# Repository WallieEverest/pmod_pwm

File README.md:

# Overview

This circuit is a PWM audio filter for the TT04 ChipTune project.
ChipTune replicates the Audio Processing Unit (APU) of vintage video games.
Separate PWM outputs are provided for each sound engine, allowing NES game music to be externally mixed into stereo or surround sound.
Resistor values will be tailored for balancing channel volume.

The primary interface is PMOD connectors to the TT04 Breakout Board. Final layout is pending assignment of all three PMOD connectors.

Based on data from:
- https://github.com/WallieEverest/tt04

## Interface

- UI_IN PMOD
- UO_OUT PMOD
- UIO PMOD (unused)
- USB-B for serial UART control of the Tiny Tapeout project
- JST 3-pin connector for low-level stereo preamp
- Onboard speaker for demonstrations

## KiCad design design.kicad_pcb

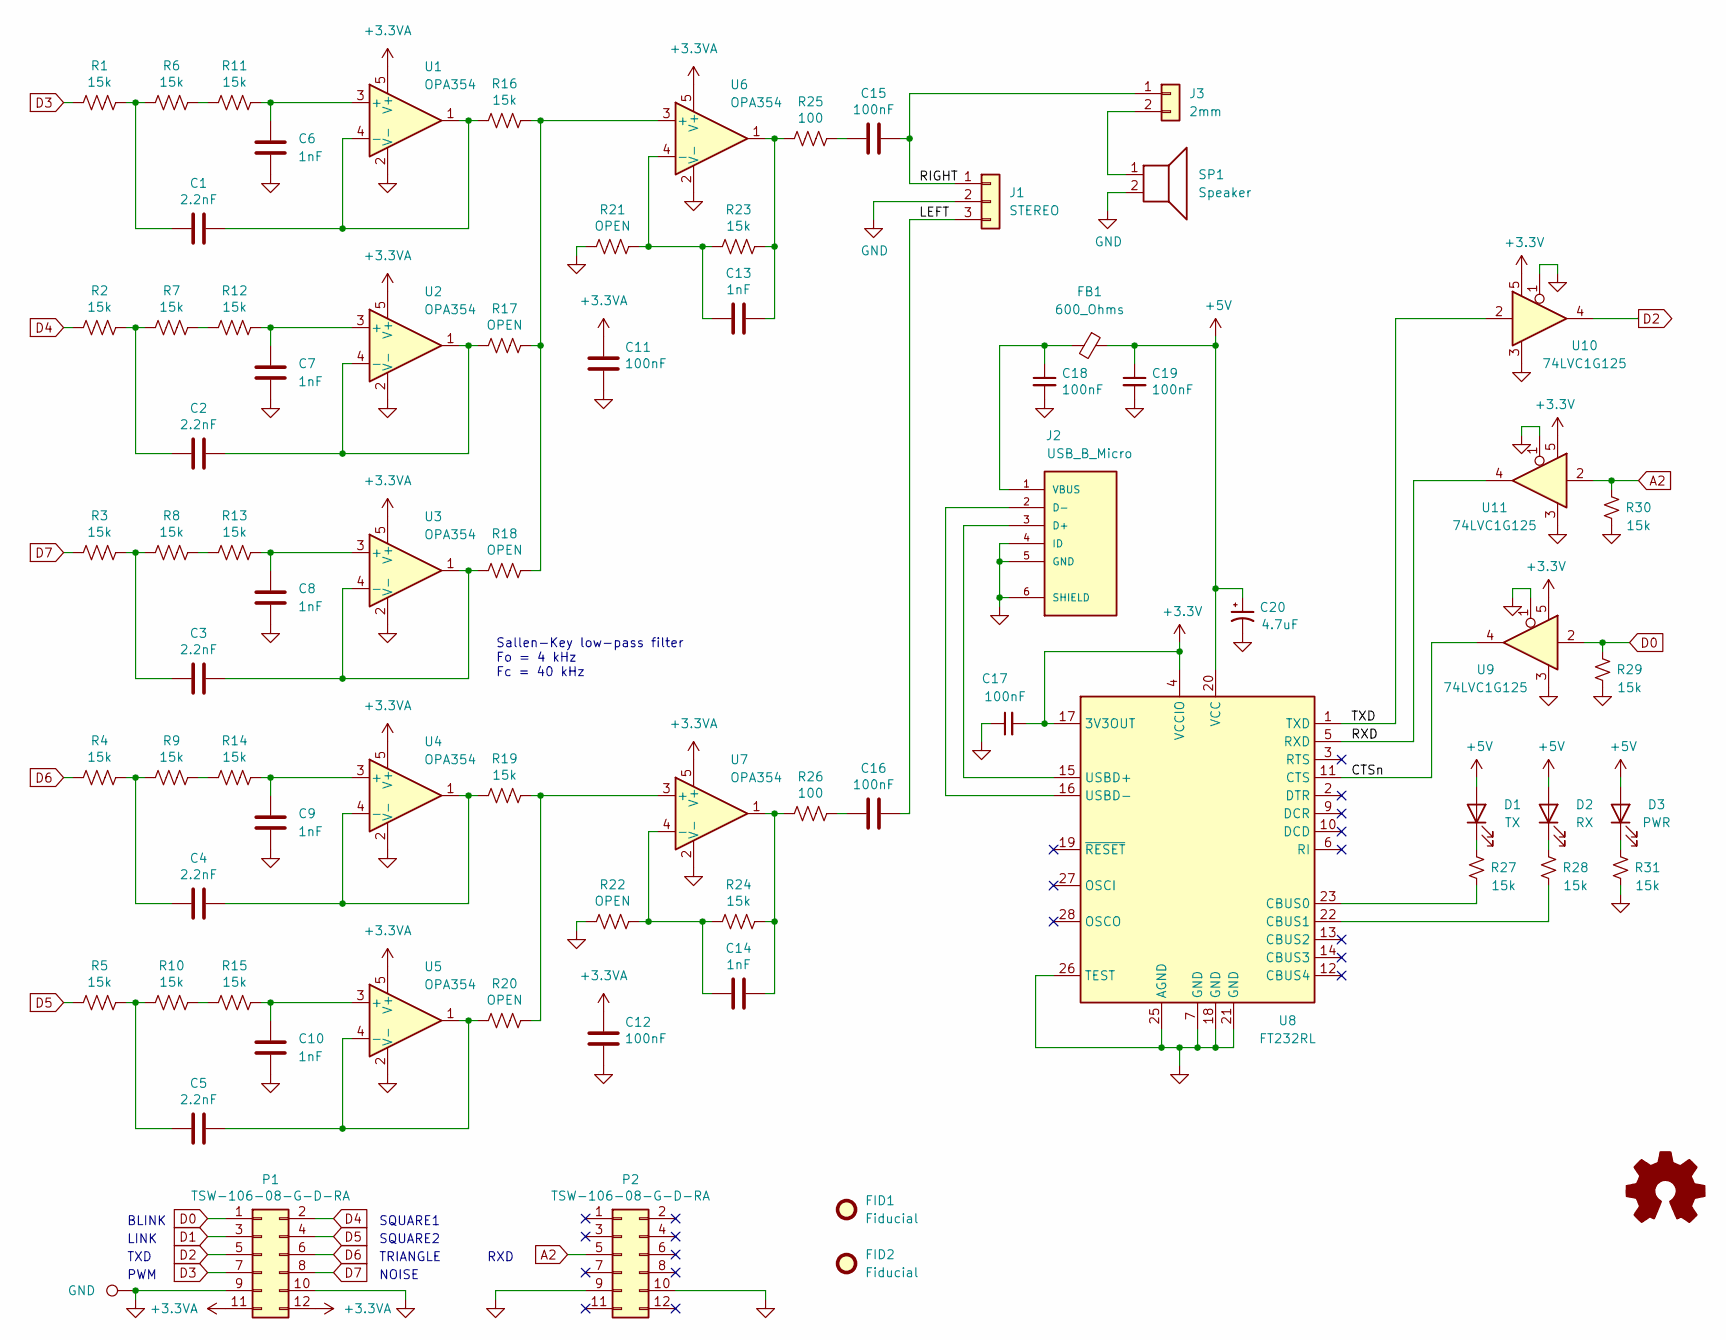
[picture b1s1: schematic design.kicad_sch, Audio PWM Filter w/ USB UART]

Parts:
C1, C2, C3, C4, C5: 2.2nF; C_0402_1005Metric; LCSC C913886
C6, C7, C8, C9, C10, C13, C14: 1nF; C_0402_1005Metric; LCSC C1523
C11, C12, C15, C16, C17, C18, C19: 100nF; C_0402_1005Metric; LCSC C1525
C20: 4.7uF; C_0603_1608Metric; LCSC C19666
D1: TX; LED_0805_2012Metric_Castellated; LCSC C2297
D2: RX; LED_0805_2012Metric_Castellated; LCSC C2297
D3: PWR; LED_0805_2012Metric_Castellated; LCSC C2297
FB1: 600_Ohms; L_0805_2012Metric; LCSC C1017
FID1, FID2: Fiducial; Fiducial_0.75mm_Mask1.5mm; LCSC None
J1: STEREO; JST_SH_BM03B-SRSS-TB_1x03-1MP_P1.00mm_Vertical; LCSC C160389
J2: USB_B_Micro; SHOUHAN_MICROXNJ; LCSC C404969
J3: 2mm; PinHeader_1x02_P2.00mm_Vertical_SMD_Pin1Left; LCSC C917549
P1, P2: TSW-106-08-G-D-RA; PinHeader_2x06_PMOD; LCSC C706887
R1, R2, R3, R4, R5, R6, R7, R8, R9, R10, R11, R12, R13, R14, R15, R16, R19, R23, R24, R27, R28, R29, R30, R31: 15k; R_0402_1005Metric; LCSC C25756
R17, R18, R20, R21, R22: OPEN; R_0402_1005Metric; LCSC C26083
R25, R26: 100; R_0402_1005Metric; LCSC C25076
SP1: Speaker; speaker_fs_1340; LCSC C482342
TP1: GND; TestPoint_Keystone_5019_Minature; LCSC C5199800
U1, U2, U3, U4, U5, U6, U7: OPA354; SOT-23-5_OPA; LCSC C36384
U8: FT232RL; SSOP-28_5.3x10.2mm_P0.65mm; LCSC C8690
U9, U10, U11: 74LVC1G125; SOT-23-5; LCSC C23654

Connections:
+3.3VA: C11.1, C12.1, P1.11, P1.12, U1.5 (V+), U2.5 (V+), U3.5 (V+), U4.5 (V+), U5.5 (V+), U6.5 (V+), U7.5 (V+)
+3V3: C17.2, U8.4 (VCCIO), U8.17 (3V3OUT), U9.5 (VCC), U10.5 (VCC), U11.5 (VCC)
+5V: C19.1, C20.1, D1.2 (A), D2.2 (A), D3.2 (A), FB1.1, U8.20 (VCC)
/CTSn: U8.11 (CTS), U9.4
/LEFT: C16.1, J1.3
/RIGHT: C15.1, J1.1, J3.1
/RXD: U8.5 (RXD), U11.4
/TXD: U8.1 (TXD), U10.2
A2: P2.5, R30.2, U11.2
D0: P1.1, R29.2, U9.2
D1: P1.3
D2: P1.5, U10.4
D3: P1.7, R1.2
D4: P1.2, R2.2
D5: P1.4, R5.2
D6: P1.6, R4.2
D7: P1.8, R3.2
GND: C6.2, C7.2, C8.2, C9.2, C10.2, C11.2, C12.2, C17.1, C18.2, C19.2, C20.2, J1.2, J2.4 (ID), J2.5 (GND), J2.6 (SHIELD), P1.9, P1.10, P2.9, P2.10, R21.2, R22.2, R29.1, R30.1, R31.1, SP1.2, TP1.1, U1.2 (V-), U2.2 (V-), U3.2 (V-), U4.2 (V-), U5.2 (V-), U6.2 (V-), U7.2 (V-), U8.7 (GND), U8.18 (GND), U8.21 (GND), U8.25 (AGND), U8.26 (TEST), U9.1, U9.3 (GND), U10.1, U10.3 (GND), U11.1, U11.3 (GND)
unnamed: C1.2, R1.1, R6.2
unnamed: C2.2, R2.1, R7.2
unnamed: C3.2, R3.1, R8.2
unnamed: C4.2, R4.1, R9.2
unnamed: C5.2, R5.1, R10.2
unnamed: C13.1, R23.1, R25.2, U6.1
unnamed: C14.1, R24.1, R26.2, U7.1
unnamed: C15.2, R25.1
unnamed: C16.2, R26.1
unnamed: D1.1 (K), R27.2
unnamed: D2.1 (K), R28.2
unnamed: D3.1 (K), R31.2
unnamed: J2.3 (D+), U8.15 (USBD+)
unnamed: J2.2 (D-), U8.16 (USBD-)
unnamed: C18.1, FB1.2, J2.1 (VBUS)
unnamed: J3.2, SP1.1
unnamed: R10.1, R15.2
unnamed: R6.1, R11.2
unnamed: R7.1, R12.2
unnamed: R8.1, R13.2
unnamed: R9.1, R14.2
unnamed: C6.1, R11.1, U1.3 (+)
unnamed: C1.1, R16.2, U1.1, U1.4 (-)
unnamed: C7.1, R12.1, U2.3 (+)
unnamed: C2.1, R17.2, U2.1, U2.4 (-)
unnamed: C8.1, R13.1, U3.3 (+)
unnamed: C3.1, R18.2, U3.1, U3.4 (-)
unnamed: C9.1, R14.1, U4.3 (+)
unnamed: C4.1, R19.2, U4.1, U4.4 (-)
unnamed: C10.1, R15.1, U5.3 (+)
unnamed: C5.1, R20.2, U5.1, U5.4 (-)
unnamed: R16.1, R17.1, R18.1, U6.3 (+)
unnamed: C13.2, R21.1, R23.2, U6.4 (-)
unnamed: R19.1, R20.1, U7.3 (+)
unnamed: C14.2, R22.1, R24.2, U7.4 (-)
unnamed: R27.1, U8.23 (CBUS0)
unnamed: R28.1, U8.22 (CBUS1)

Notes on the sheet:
NOISE
LINK
Sallen-Key low-pass filter Fo = 4 kHz Fc = 40 kHz
TRIANGLE
RXD
BLINK
SQUARE1
PWM
TXD
SQUARE2

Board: 4 copper layers, 75 parts (0 on the bottom side), 54 nets, no tracks yet.
